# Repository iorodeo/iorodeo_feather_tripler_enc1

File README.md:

# IO Rodeo's iorodeo_feather_tripler_enc1  

Hardware files for IO Rodeo's iorodeo_feather_tripler_enc1. (In progress)

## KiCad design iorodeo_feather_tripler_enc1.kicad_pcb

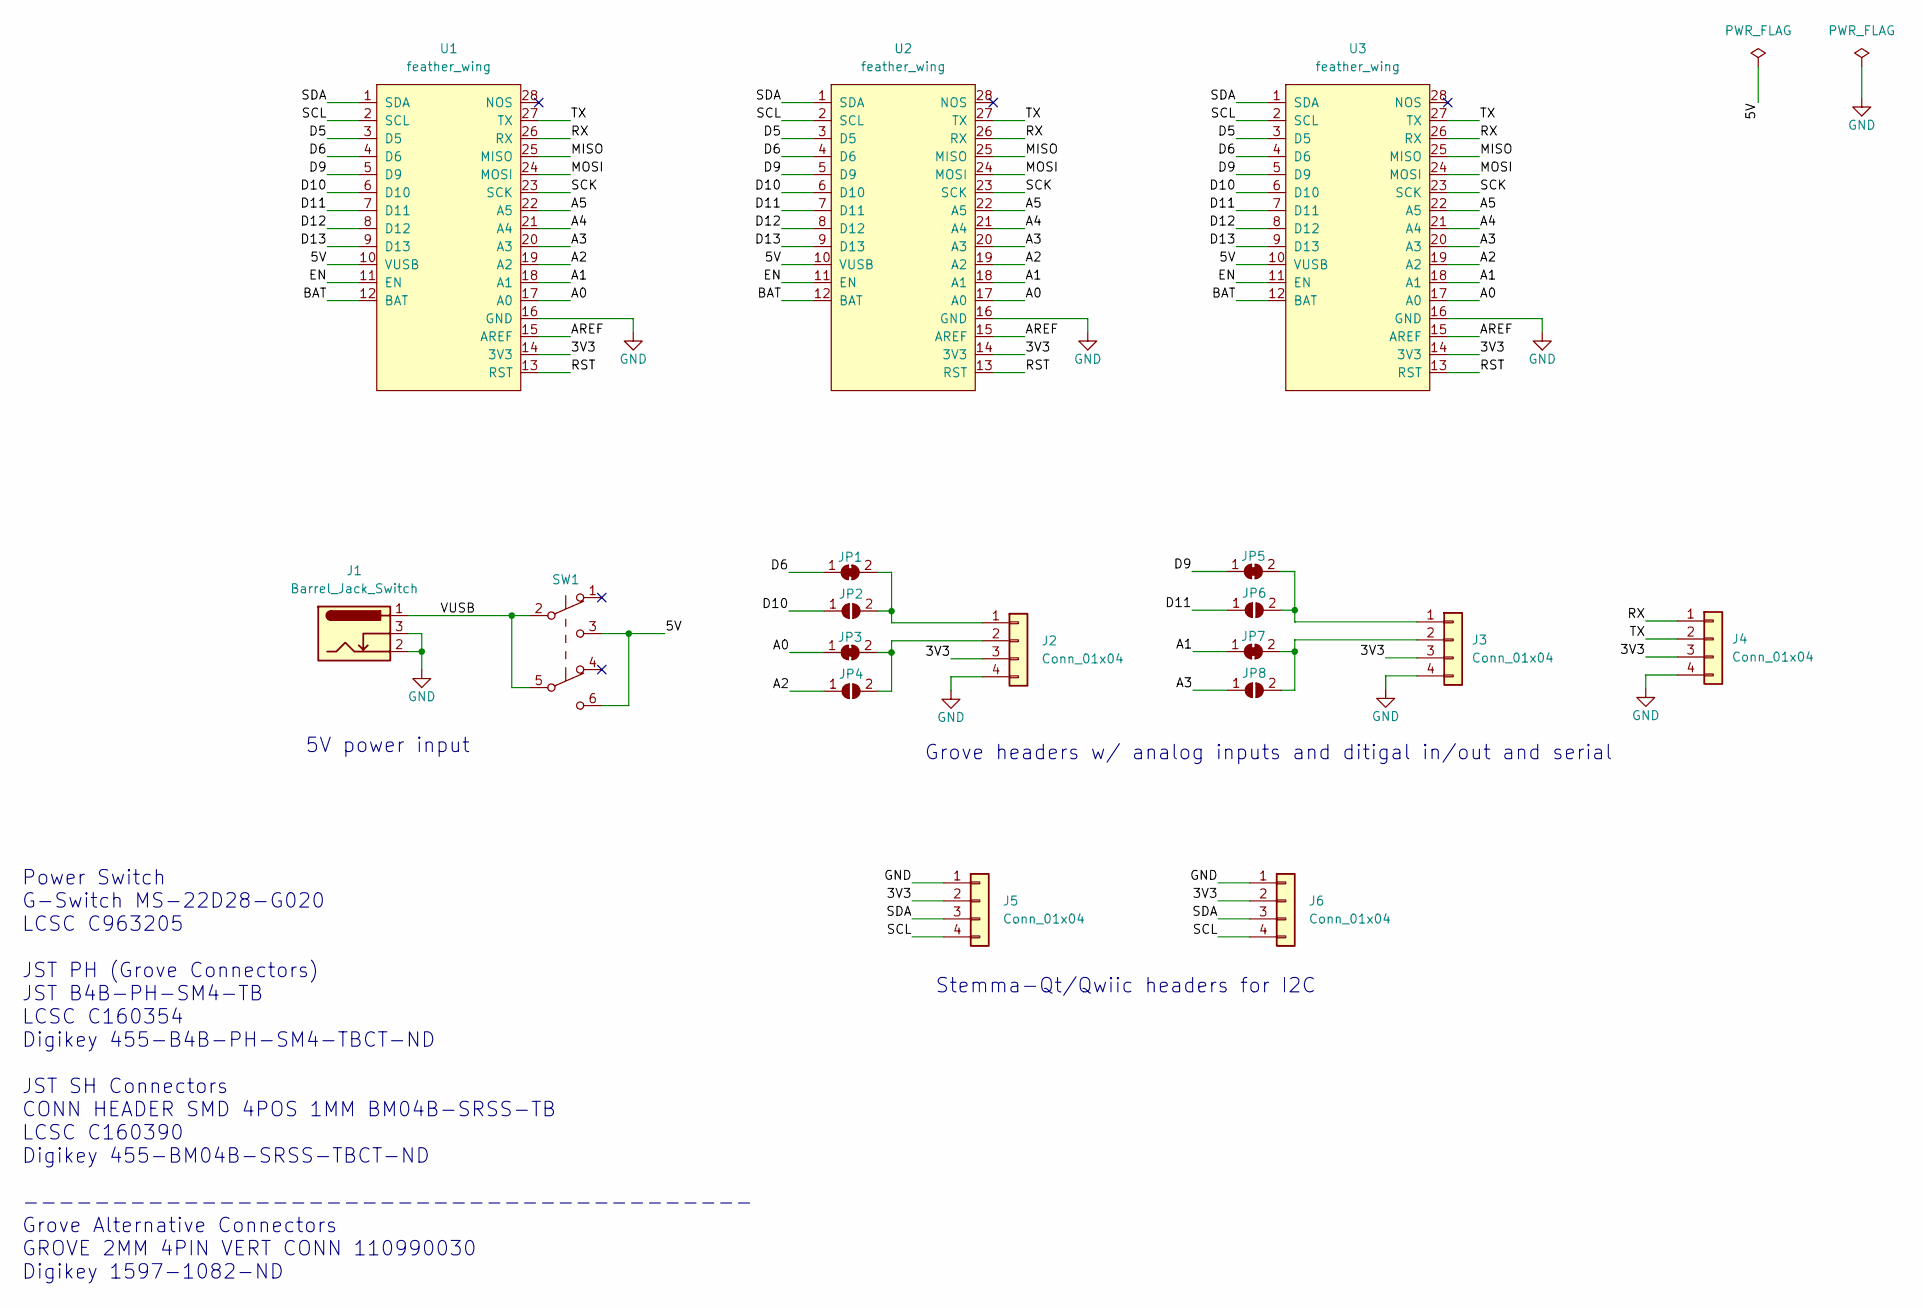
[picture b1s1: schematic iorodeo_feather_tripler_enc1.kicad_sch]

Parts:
J1: Barrel_Jack_Switch; CUI_PJ-035C
J2, J3, J4: Conn_01x04; JST_PH_B4B-PH-SM4-TB_1x04-1MP_P2.00mm_Vertical
J5, J6: Conn_01x04; JST_SH_BM04B-SRSS-TB_1x04-1MP_P1.00mm_Vertical
JP1, JP3, JP5, JP7: SolderJumper_2_Bridged; SolderJumper-2_P1.3mm_Bridged_RoundedPad1.0x1.5mm
JP2, JP4, JP6, JP8: SolderJumper_2_Open; SolderJumper-2_P1.3mm_Open_RoundedPad1.0x1.5mm
SW1: SW_Push_DPDT; MS-22D28-G020
U1, U2, U3: feather_wing

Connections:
/3V3: J2.3, J3.3, J4.3, J5.2, J6.2, U1.14 (3V3), U2.14 (3V3), U3.14 (3V3)
/5V: SW1.3 (C), SW1.6 (C), U1.10 (VUSB), U2.10 (VUSB), U3.10 (VUSB)
/A0: JP3.1 (A), U1.17 (A0), U2.17 (A0), U3.17 (A0)
/A1: JP7.1 (A), U1.18 (A1), U2.18 (A1), U3.18 (A1)
/A2: JP4.1 (A), U1.19 (A2), U2.19 (A2), U3.19 (A2)
/A3: JP8.1 (A), U1.20 (A3), U2.20 (A3), U3.20 (A3)
/A4: U1.21 (A4), U2.21 (A4), U3.21 (A4)
/A5: U1.22 (A5), U2.22 (A5), U3.22 (A5)
/AREF: U1.15 (AREF), U2.15 (AREF), U3.15 (AREF)
/BAT: U1.12 (BAT), U2.12 (BAT), U3.12 (BAT)
/D5: U1.3 (D5), U2.3 (D5), U3.3 (D5)
/D6: JP1.1 (A), U1.4 (D6), U2.4 (D6), U3.4 (D6)
/D9: JP5.1 (A), U1.5 (D9), U2.5 (D9), U3.5 (D9)
/D10: JP2.1 (A), U1.6 (D10), U2.6 (D10), U3.6 (D10)
/D11: JP6.1 (A), U1.7 (D11), U2.7 (D11), U3.7 (D11)
/D12: U1.8 (D12), U2.8 (D12), U3.8 (D12)
/D13: U1.9 (D13), U2.9 (D13), U3.9 (D13)
/EN: U1.11 (EN), U2.11 (EN), U3.11 (EN)
/MISO: U1.25 (MISO), U2.25 (MISO), U3.25 (MISO)
/MOSI: U1.24 (MOSI), U2.24 (MOSI), U3.24 (MOSI)
/RST: U1.13 (RST), U2.13 (RST), U3.13 (RST)
/RX: J4.1, U1.26 (RX), U2.26 (RX), U3.26 (RX)
/SCK: U1.23 (SCK), U2.23 (SCK), U3.23 (SCK)
/SCL: J5.4, J6.4, U1.2 (SCL), U2.2 (SCL), U3.2 (SCL)
/SDA: J5.3, J6.3, U1.1 (SDA), U2.1 (SDA), U3.1 (SDA)
/TX: J4.2, U1.27 (TX), U2.27 (TX), U3.27 (TX)
/VUSB: J1.1, SW1.2 (B), SW1.5 (B)
GND: J1.2, J1.3, J2.4, J3.4, J4.4, J5.1, J6.1, U1.16 (GND), U2.16 (GND), U3.16 (GND)
unnamed: J2.1, JP1.2 (B), JP2.2 (B)
unnamed: J2.2, JP3.2 (B), JP4.2 (B)
unnamed: J3.1, JP5.2 (B), JP6.2 (B)
unnamed: J3.2, JP7.2 (B), JP8.2 (B)

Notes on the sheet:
Power Switch G-Switch MS-22D28-G020 LCSC C963205 JST PH (Grove Connectors) JST B4B-PH-SM4-TB LCSC C160354 Digikey 455-B4B-PH-SM4-TBCT-ND JST SH Connectors CONN HEADER SMD 4POS 1MM BM04B-SRSS-TB LCSC C160390 Digikey 455-BM04B-SRSS-TBCT-ND ----------------------------------------- Grove Alternative C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
Grove headers w/ analog inputs and ditigal in/out and serial
5V power input
Stemma-Qt/Qwiic headers for I2C

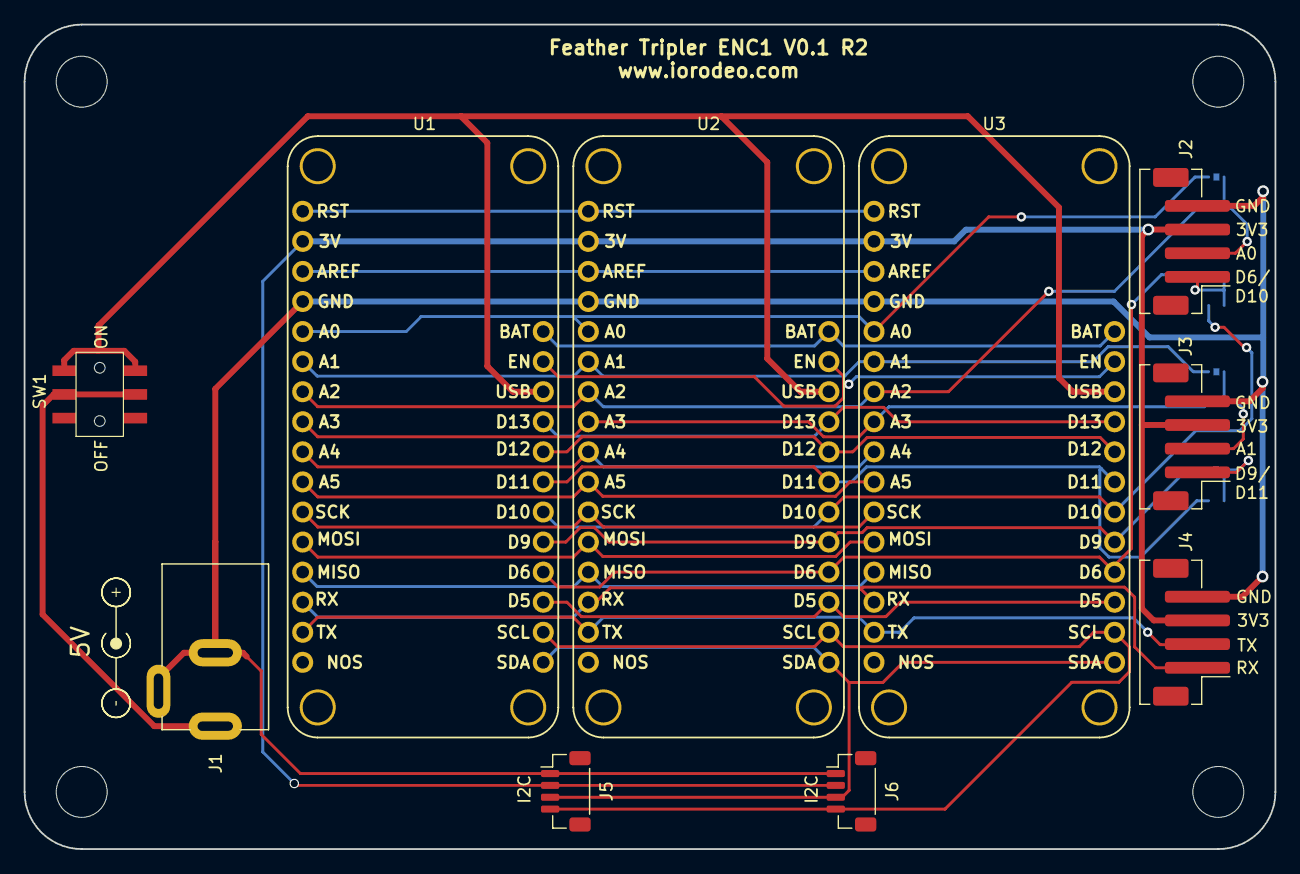
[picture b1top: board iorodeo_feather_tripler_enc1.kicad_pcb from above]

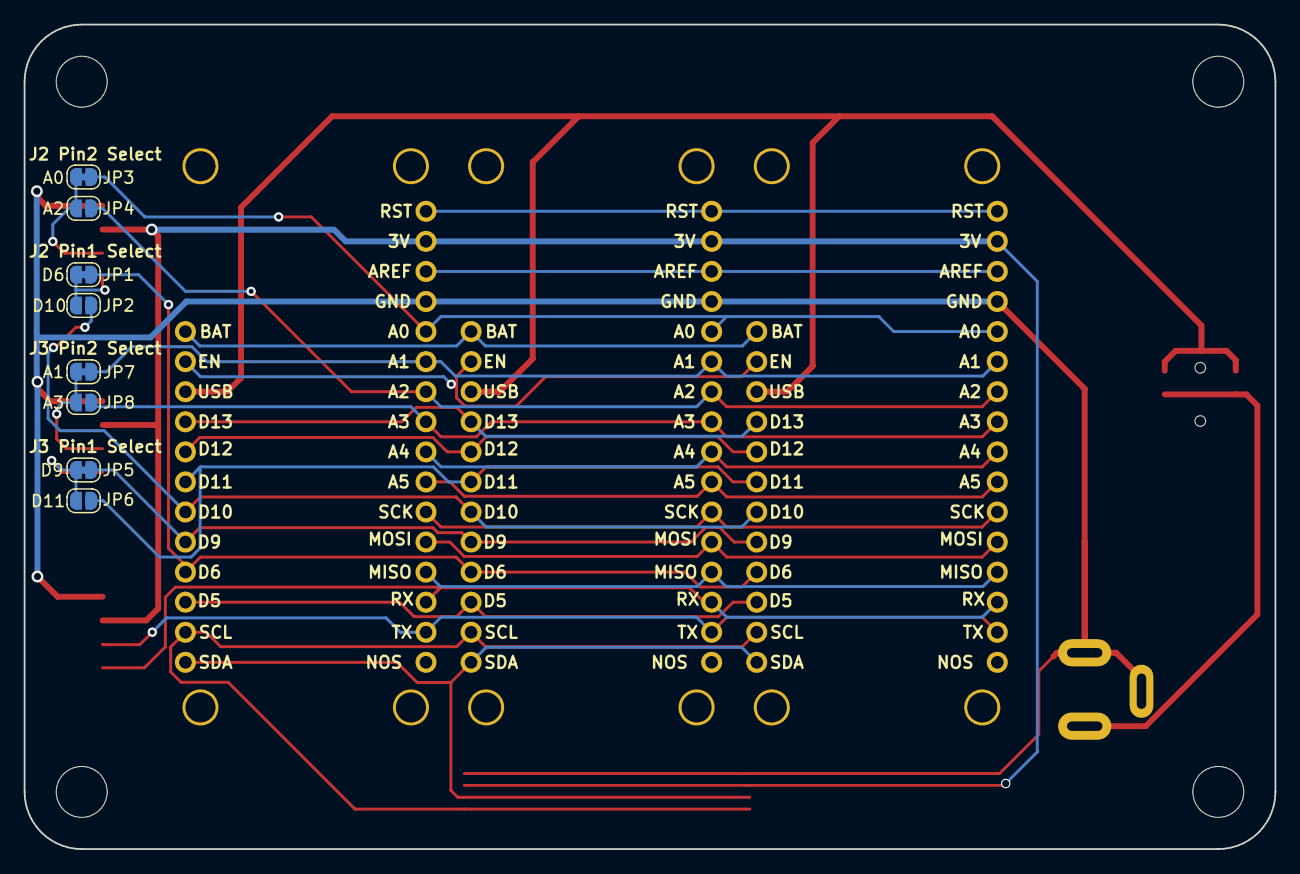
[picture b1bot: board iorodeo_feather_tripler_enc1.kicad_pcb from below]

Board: 2 copper layers, 105.7 x 69.6 mm, 22 parts (8 on the bottom side), 32 nets.

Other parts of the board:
M1, M2, M3, M4: MountingHole_4.3mm_M4

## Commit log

2024-08-19 Project creation.
2024-08-19 Updated readme and license.
2024-08-19 Fixed issues with JST PH header orientation.
2024-09-04 Added an image folder and image of PCB v0.1 R1
2024-09-04 Modified READ.ME to add a project image.
2024-09-08 Worked on revision 2.
2024-09-08 More work on revision 2. Added jumper pads to grove headers.
2024-09-08 Assigned footprints for jumper pads.
2024-09-08 Finished rerouting board. Remade production files. Need to be checked.
2024-09-09 Fixed issues in silkscreen. Remade gerbers.
2024-09-09 Fixed another issue in silkscreen and remade gerbers.
2024-09-29 Added project BOM.
2024-09-29 Cleaned up a bit.
2024-10-02 Added PCB and enclosure images.
2024-10-02 Update image link in README file
2024-10-02 Removed an old image.
